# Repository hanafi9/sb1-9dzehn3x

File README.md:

# sb1-9dzehn3x

[Edit in StackBlitz next generation editor ⚡️](https://stackblitz.com/~/github.com/hanafi9/sb1-9dzehn3x)

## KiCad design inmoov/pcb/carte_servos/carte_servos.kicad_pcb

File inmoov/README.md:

# InMoov : Raspberry Pi 5 + Coral USB

Deux programmes qui tournent **à côté de MyRobotLab (Nixie)** sur le Raspberry Pi 5
et lui parlent par son API REST (`http://127.0.0.1:8888/api/service/...`) :

| Programme | Rôle | Python |
|---|---|---|
| `vision/face_tracker.py` | Caméra USB → Coral USB → tourne `rothead` / `neck` vers le visage le plus proche | **3.12** (PyCoral n'existe pas pour 3.13 ; installé par `vision/install_coral.sh`) |
| `voice/speech_listener.py` | Micro → détection de voix → Whisper → commandes locales, **IA Claude** ou chatbot `i01.chatBot` | 3.11 (celui du système) |
| `voice/llm_brain.py` | IA conversationnelle (Claude) qui remplace le chatbot AIML et peut bouger la tête et les mains | 3.11 |
| `legs/` | Jambes motorisées : firmware Arduino Mega, pilotage depuis le Pi, calcul des moteurs | Arduino + 3.11 |
| `app/` | **Atelier InMoov** : application web pour tout monter, programmer et régler (voir section 0) | 3.11 |

```
 Caméra USB ─► face_tracker.py (Coral) ──┐  POST /api/service/i01.head.rothead/moveTo [95.0]
                                         ├─► MyRobotLab Nixie (InMoov2) ─► Arduino Mega ─► servos
 Micro USB ──► speech_listener.py ───────┘  POST /api/service/i01.chatBot/getResponse ["bonjour"]
                                                         └─► htmlFilter ─► i01.mouth (synthèse vocale)
```

## 0. Atelier InMoov : l'application qui regroupe tout

Une application web qui tourne sur le Raspberry Pi et s'ouvre depuis un téléphone, une
tablette ou un PC du même réseau : `http://<adresse-du-pi>:8090`.

| Onglet | Ce qu'il fait |
|---|---|
| **Tableau de bord** | État de MyRobotLab, du Coral, des ports série, des services, avancement du montage |
| **Banc d'essai** | Tout tester sur une page : **silhouette du robot cliquable** (tête, torse, bras, mains) avec curseurs et balayage de chaque servo, bilan ✓/✗ qui colore la silhouette, **les 2 caméras en direct** avec les cadres des visages et objets vus par le Coral, haut-parleurs gauche/droite, **faire parler** le robot (Piper), niveau du **micro**, « tout au repos » et **arrêt** (servos coupés). 2e caméra : `vision.second_camera_index` |
| **Documentation** | **Le manuel complet** : un chapitre par partie du corps (tête et cou, torse et électronique, bras, mains, bassin, jambes, capteurs) avec rôle, servos, schéma de câblage, pièces, montage pas à pas, réglages, test final, problèmes fréquents et liens officiels ; plus logiciel, IA, dépannage général et tous les liens. Recherche intégrée et bouton « Tout imprimer / PDF ». Version PDF prête : [docs/manuel-inmoov.pdf](docs/manuel-inmoov.pdf) |
| **Guide de montage** | 43 étapes en 10 phases (Pi, MyRobotLab, électronique, tête et cou, bras/mains/torse, vision, voix et IA, jambes, mise en service, nouveautés IA et capteurs), à cocher, avec les commandes à copier |
| **Schémas** | Un schéma de câblage par partie (tête, torse, bras, mains, bassin, jambes) généré automatiquement, la liste des servos (modèle, carte, canal), les **pièces imprimées à cocher**, le matériel, et l'**électronique simplifiée** : une seule Arduino Mega + 3 cartes PCA9685, avec le script MyRobotLab qui rattache chaque servo à sa carte |
| **Schémas électriques** (dans l'onglet Schémas) | **8 schémas détaillés** : alimentation générale, tête, cou, torse, bras, mains, bassin, jambes. Chaque fil, chaque broche, chaque fusible, avec la **liste de câblage** (de → à, type, couleur, section) et les points de vigilance. PDF prêt : [docs/schemas-electriques.pdf](docs/schemas-electriques.pdf). **Projet KiCad** : dossier [kicad/](kicad/LISEZMOI.md) ou bouton « Projet KiCad (.zip) » |
| **Circuits imprimés « DOMOKAMI CONNECT »** | Prêts à commander, avec Gerber, liste des composants, contrôle KiCad (0 erreur) et mode d'emploi : [shield jambes](pcb/shield_jambes/LISEZMOI.md) pour l'Arduino Mega n°2 ; [carte servos 16 voies](pcb/carte_servos/LISEZMOI.md) × 3 (PCA9685 + fusible + mesure de courant, puces posées par JLCPCB) ; [HAT capteurs](pcb/hat_capteurs/LISEZMOI.md) pour le Raspberry Pi 5 (3 ADS1115 + 10 entrées FSR + 3 sorties I2C) |
| **Capteurs** | Courant et tension de chaque carte (coupure automatique si un servo force), batterie, toucher au bout des doigts, présence, bouton « prise douce » |
| **IA** | État de l'IA (Claude, vision, IA locale, voix Piper, LED), **souvenirs** du robot (à consulter ou effacer), **gestes appris** à rejouer |
| **Servos** | Les 31 servos d'InMoov2 (tête et cou, torse, bras, mains) : curseur pour bouger, repos, activer/désactiver, lire la position, **calibration** (min, max, repos, vitesse, sens), envoi à MyRobotLab et enregistrement de sa configuration |
| **Arduino** | Voir le code, **compiler et téléverser** MrlComm (les deux Mega du haut du corps) et le firmware des jambes, installer le cœur AVR et les bibliothèques, détecter les cartes branchées |
| **Jambes** | Connexion à l'Arduino des jambes, état de chaque servo (position, charge, température, tension), RESET, FIGER, couple, poses et séquences (mouvement seulement si « robot sur portique » est coché), **pieds et équilibre** : poids et centre de pression de chaque pied, tare, équilibre surveillé ou actif |
| **Services** | Démarrer, arrêter et voir le journal du suivi de visage et de la voix |
| **Réglages** | Adresse et dossier de MyRobotLab, arduino-cli, édition **vérifiée** de `config.json` et de la config des jambes (copie `.bak` à chaque enregistrement) |

### Électronique simplifiée (onglet Schémas)

Au lieu de brancher chaque servo sur deux Arduino Mega, on utilise **une seule Mega** (i01.left,
programme MrlComm) et **3 cartes PCA9685** de 16 voies reliées par un bus I2C à 4 fils
(service MyRobotLab `Adafruit16CServoDriver`) :

| Carte | Adresse | Pont à souder | Servos |
|---|---|---|---|
| A | 0x40 | aucun | tête (8) + ventre (3) |
| B | 0x41 | A0 | bras gauche (4) + main gauche (6) |
| C | 0x42 | A1 | bras droit (4) + main droite (6) |

Le bouton **« Appliquer à MyRobotLab »** (ou le script à coller dans l'onglet Python de MyRobotLab)
crée les 3 cartes, les attache à `i01.left` en I2C (`attach("i01.left", "0", "0x40")`, comme dans
l'exemple officiel de MyRobotLab) puis fait pour chaque servo `detach()`, `setPin(canal)`, `attach(carte)`.
Enregistrez ensuite la config MyRobotLab (onglet Servos).

Pourquoi passer par l'Arduino et pas directement par le Raspberry Pi 5 ? Le service RasPi de
MyRobotLab repose sur Pi4J 1.x / wiringPi, qui ne gère pas le Pi 5.

Alimentation : 6 V forte puissance → bornier avec un fusible par carte ; pour les gros servos,
+ et − pris directement sur le bornier et seulement le signal sur la carte ; masses toutes reliées.

### Installation

```bash
cd ~/domokami/inmoov
python3 -m venv .venv-app
.venv-app/bin/pip install -r app/requirements.txt
sudo usermod -aG dialout $USER         # accès aux ports série (Arduino), puis redémarrer

# arduino-cli (compilation et téléversement depuis l'appli)
curl -fsSL https://raw.githubusercontent.com/arduino/arduino-cli/master/install.sh | BINDIR=$HOME/.local/bin sh

# mot de passe de l'appli (conseillé : elle peut bouger le robot et reprogrammer les cartes)
echo 'INMOOV_APP_PASSWORD=choisissez-un-mot-de-passe' > app.env && chmod 600 app.env

cd app && set -a && . ../app.env && set +a && ../.venv-app/bin/python app.py
```

Pour que les boutons Démarrer / Arrêter de l'onglet Services fonctionnent, autorisez **uniquement**
ces commandes sans mot de passe (`sudo visudo -f /etc/sudoers.d/inmoov`), en remplaçant
`VOTRE_UTILISATEUR` par votre nom d'utilisateur (la commande `whoami` l'affiche) :

```
VOTRE_UTILISATEUR ALL=(root) NOPASSWD: /usr/bin/systemctl start inmoov-vision, /usr/bin/systemctl stop inmoov-vision, /usr/bin/systemctl restart inmoov-vision, /usr/bin/systemctl start inmoov-voice, /usr/bin/systemctl stop inmoov-voice, /usr/bin/systemctl restart inmoov-voice, /usr/bin/systemctl start inmoov-sensors, /usr/bin/systemctl stop inmoov-sensors, /usr/bin/systemctl restart inmoov-sensors
```

Démarrage automatique : service `systemd/inmoov-app.service` (voir section 5).

**Sans ligne de commande** : onglet Services → « Programmes du robot ». L'Atelier lance lui-même
MyRobotLab, les caméras (Coral), la voix et les capteurs, avec leurs journaux en direct
(`app/data/logs/`). Cochez « au démarrage de l'Atelier » pour qu'ils se lancent tout seuls ; il suffit
alors d'installer le seul service de l'Atelier : `bash systemd/install.sh` puis
`sudo systemctl enable --now inmoov-app`.

### Bon à savoir

- Le curseur d'un servo envoie une valeur **de 0 à 180** que MyRobotLab convertit entre **min** et
  **max** (c'est le fonctionnement d'InMoov2). Les valeurs par défaut affichées viennent du code
  de MyRobotLab (InMoov2HeadConfig, InMoov2ArmConfig, InMoov2HandConfig, InMoov2TorsoConfig).
- « Enregistrer + appliquer » envoie `setMinMaxOutput`, `setInverted`, `setRest` et `setSpeed` au servo ;
  « Enregistrer la config MyRobotLab » appelle `runtime.saveConfig` pour que ce soit conservé au redémarrage.
- MrlComm est pris dans le dossier de MyRobotLab (`<mrl_dir>/resource/Arduino/MrlComm`) pour être
  toujours de la même version que MyRobotLab. **Arrêtez MyRobotLab** (ou déconnectez la carte) avant
  de téléverser : le port série ne peut pas servir à deux programmes.
- Testée avec un faux MyRobotLab et un faux Arduino des jambes : le firmware des jambes a été
  **réellement compilé depuis l'appli**. Elle n'a pas encore été essayée avec le vrai robot.

## 1. Préparer le Raspberry Pi 5

- Raspberry Pi OS **64 bits** (Bookworm ou Trixie), alimentation officielle **5 V / 5 A**
  (sinon les ports USB sont limités à 600 mA, insuffisant pour Coral + caméra + micro).
- Brancher le **Coral USB sur un port USB 3 (bleu)**.
- MyRobotLab Nixie installé et InMoov2 démarré (WebGui sur le port 8888).
- **Désactiver le suivi de visage intégré d'InMoov2** pour ne pas avoir deux programmes qui
  bougent la tête en même temps.

Télécharger le projet sur le Pi (il arrive dans `~/domokami/inmoov`, quel que soit votre nom
d'utilisateur), puis :

```bash
sudo apt install -y git python3-venv
git clone --branch claude/inspiring-fermi-0kap3c https://github.com/hanafi9/sb1-9dzehn3x.git ~/domokami
cd ~/domokami/inmoov
cp config.example.json config.json   # puis l'adapter à votre robot
```

Mettre à jour plus tard : `cd ~/domokami && git pull` (config.json et les fichiers .env sont conservés).

## 2. Vision : Coral USB + suivi de visage

### Installation (pilote + Python + modèle) : un seul script

```bash
cd ~/domokami/inmoov
bash vision/install_coral.sh        # sans sudo ; redémarrer le Pi s'il le demande
```

Le script installe :
1. le pilote **libedgetpu** ;
2. **Python 3.12** (avec [uv](https://docs.astral.sh/uv/), à côté du Python du système) ;
3. **pycoral**, **tflite-runtime** et OpenCV dans `.venv-vision` ;
4. le modèle de détection de visage.

Il vérifie l'empreinte SHA-256 de chaque fichier téléchargé et finit par afficher le Coral vu
par PyCoral.

> Pourquoi pas les paquets de Google ? Le dépôt apt Coral de Google répond « 403 Forbidden »
> depuis fin septembre 2026, et le PyCoral officiel s'arrête à Python 3.9. Le script prend les
> versions recompilées par la communauté : [feranick/libedgetpu](https://github.com/feranick/libedgetpu/releases)
> (paquet Debian 13 « trixie »), [feranick/pycoral](https://github.com/feranick/pycoral/releases) et
> [feranick/TFlite-builds](https://github.com/feranick/TFlite-builds/releases).

`lsusb` affiche `1a6e:089a Global Unichip` tant que le Coral n'a pas servi, puis
`18d1:9302 Google` une fois initialisé par le suivi de visage (il passe alors en USB 3).
⚠️ Le Coral peut consommer jusqu'à 900 mA : alimentation officielle 27 W (5 A) ou hub USB alimenté.

### Modèle de détection de visage

Déjà téléchargé par `install_coral.sh` dans `models/`. À la main :

```bash
mkdir -p models
wget -P models https://raw.githubusercontent.com/google-coral/test_data/master/ssd_mobilenet_v2_face_quant_postprocess_edgetpu.tflite
```

### Lancer

```bash
cd vision
../.venv-vision/bin/python face_tracker.py --config ../config.json --dry-run -v   # test sans bouger la tête
../.venv-vision/bin/python face_tracker.py --config ../config.json
```

### Réglages (`config.json` → `vision`)

| Clé | Effet |
|---|---|
| `pan.invert` / `tilt.invert` | La tête part dans le mauvais sens ? Passez à `true` / `false`. |
| `gain` | Vitesse de réaction. Trop grand = la tête oscille ; trop petit = elle traîne. |
| `deadband` | Zone morte au centre de l'image (0.08 = 8 %), pour éviter les tremblements. |
| `max_step` | Nombre maximum de degrés par commande (protège les servos). |
| `min` / `max` | **Mettez les mêmes limites que dans MyRobotLab** pour ne jamais forcer la mécanique. |
| `show_window` | `true` pour voir l'image et les visages détectés (écran nécessaire). |

## 3. Reconnaissance vocale améliorée

Améliorations par rapport à la reconnaissance d'origine :

1. **Whisper (faster-whisper) hors ligne** : bien meilleur en français, pas besoin d'Internet.
2. **Détection de voix (WebRTC VAD)** : Whisper n'est appelé que quand quelqu'un parle,
   ce qui économise le processeur et évite les phrases inventées sur le bruit des servos.
3. **Filtres anti-erreurs** : on ignore les segments à faible confiance et les « hallucinations »
   connues de Whisper en français (« Sous-titres réalisés par la communauté d'Amara.org »...).
4. **Mot de réveil tolérant** : « InMoov », « In Moov », « Inmove » sont tous acceptés.
   Dire juste « InMoov » → le robot répond « oui ? » et écoute la phrase suivante.
5. **Vocabulaire** (`vocabulary`) : les mots donnés aident Whisper à bien écrire les noms propres.
6. **Commandes locales** instantanées (`commands`), avec tolérance aux petites erreurs ;
   tout le reste part au chatbot d'InMoov2.
7. **Le micro est ignoré pendant que le robot parle** (durée estimée d'après la longueur de la réponse).

### Installation

```bash
sudo apt install -y libportaudio2
python3 -m venv .venv-voice
.venv-voice/bin/pip install -r voice/requirements.txt
cd voice
../.venv-voice/bin/python speech_listener.py --list-devices      # trouver le numéro du micro
../.venv-voice/bin/python speech_listener.py --config ../config.json --dry-run
```

Au premier lancement, le modèle Whisper est téléchargé (environ 150 Mo pour `base`).

### Choix du modèle Whisper (`whisper_model`)

| Modèle | Français | Vitesse sur Pi 5 |
|---|---|---|
| `tiny` | moyen | le plus rapide (≈ 2-3 s pour 10 s d'audio) |
| `base` | **bon compromis (par défaut)** | rapide |
| `small` | très bon | plus lent, à tester selon votre patience |

Les phrases adressées au robot sont courtes (2 à 4 s), donc le temps de réponse
est bien plus court que pour 10 s d'audio.

### Le matériel compte autant que le logiciel

- Un **micro USB de conférence** ou un **ReSpeaker USB Mic Array** (avec réduction de bruit)
  donne de bien meilleurs résultats qu'une webcam ou un micro jack.
- Placez le micro **loin des servos et du ventilateur** du Pi, idéalement dans la tête, orienté vers l'avant.
- Trop de fausses détections ? Montez `vad_aggressiveness` à 3.
  Le robot ne vous entend pas ? Descendez-le à 1.

## 4. IA conversationnelle (Claude) à la place du chatbot d'InMoov2

Quand `brain.enabled` vaut `true` dans `config.json`, les phrases qui ne sont pas des
commandes locales partent vers **Claude** (API Anthropic) au lieu du chatbot AIML :

- réponses naturelles en français, courtes et adaptées à la synthèse vocale ;
- **mémoire de la conversation** (remise à zéro après 10 min de silence, `reset_after_idle_s`) ;
- Claude peut **tourner la tête, ouvrir/fermer les mains, revenir au repos** (outils `move_head`,
  `hand`, `rest_position`), toujours dans les limites de `config.json` ;
- **les jambes ne sont pas accessibles à l'IA**, volontairement ;
- si Internet ou l'API ne répond pas, le robot **repasse automatiquement sur le chatbot d'InMoov2** ;
- si Claude refuse une demande, l'API la relance sur le modèle de secours recommandé
  (option `fallbacks: "default"`), sinon le robot dit poliment qu'il ne répond pas.

### Mise en route

1. Créer une clé API sur <https://platform.claude.com> (l'usage est payant, au nombre de mots traités).
2. Sur le Pi :
   ```bash
   echo 'ANTHROPIC_API_KEY=sk-ant-...' > ~/domokami/inmoov/anthropic.env
   chmod 600 ~/domokami/inmoov/anthropic.env      # ce fichier ne doit jamais aller sur GitHub
   ```
3. Dans `config.json` → `brain` : mettre votre prénom dans `owner_name`, le nom du robot dans
   `robot_name`, et éventuellement des consignes dans `extra_instructions`
   (« Tu tutoies tout le monde », « Tu adores l'astronomie »...).
4. Test sans bouger le robot : `../.venv-voice/bin/python speech_listener.py --config ../config.json --dry-run`
   (avec la clé chargée : `set -a; . ../anthropic.env; set +a`).

| Clé `brain` | Effet |
|---|---|
| `model` | `claude-opus-5-5` par défaut |
| `effort` | `low` = réponses plus rapides et moins chères (bien pour la conversation) ; `medium`/`high` = plus réfléchi mais plus lent |
| `max_tool_rounds` | nombre maximum de gestes enchaînés pour une même phrase |
| `*_service`, `*_min`, `*_max` | noms des services MyRobotLab et limites des mouvements autorisés à l'IA |

## 5. Démarrage automatique

```bash
cd ~/domokami/inmoov
bash systemd/install.sh            # adapte l'utilisateur et les chemins, puis copie les services
sudo systemctl enable --now inmoov-app inmoov-vision inmoov-voice inmoov-sensors
journalctl -u inmoov-voice -f      # voir ce que le robot entend
```

## 6. Tests (sans matériel)

```bash
python3 -m unittest discover -s tests -v
```

Ces tests vérifient l'Atelier (avec un faux MyRobotLab, si Flask est installé), la logique de suivi, le découpage audio, le mot de réveil, les commandes,
le format des appels à MyRobotLab (avec un faux serveur), le cerveau Claude (avec un faux client,
si le paquet `anthropic` est installé), les poses des jambes, la cohérence des limites
entre le Pi et le firmware Arduino, et le calcul de couple.
Ils **ne remplacent pas** un essai réel avec le Coral, la caméra et le micro.

## 7. Jambes motorisées

> ⚠️ **Sécurité d'abord.** Un robot de cette taille qui tombe se casse et peut blesser.
> Tous les essais se font **robot accroché à un portique** (sangle au niveau du bassin),
> avec un **arrêt d'urgence matériel qui coupe l'alimentation des servos**.
> Le firmware ajoute des protections, il ne remplace pas ces deux-là.

Les jambes publiées par Gaël Langevin sont prévues pour tenir debout ; il n'existe pas de
version motorisée officielle. Ce dossier fournit une base pour **12 articulations**
(6 par jambe : hanche lacet / roulis / tangage, genou, cheville tangage / roulis).

### 7.1 Choisir les moteurs : d'abord peser le robot

```bash
cd legs
python3 torque_calc.py --masse 18                 # remplacez 18 par la masse réelle portée par les jambes
python3 torque_calc.py --masse 18 --reduction 4   # avec une réduction 4:1 (poulies/engrenages)
```

Exemple **pour 18 kg** (valeur d'exemple, pas la masse de votre robot), coefficient de sécurité 1,5 :

| Articulation | Couple sans réduction | Avec réduction 4:1 |
|---|---|---|
| Genou (accroupi 40°, 2 pieds) | 176 kg·cm | 44 kg·cm |
| Hanche roulis / cheville roulis (sur 1 pied) | 243 kg·cm | 61 kg·cm |
| Cheville tangage (sur 1 pied) | 135 kg·cm | 34 kg·cm |
| Hanche tangage | 68 kg·cm | 17 kg·cm |
| Hanche lacet | 24 kg·cm | 6 kg·cm |

Actionneurs comparés (couple continu retenu ≈ 1/3 du couple de blocage quand le fabricant
ne donne pas de couple nominal) :

| Actionneur | Couple | Bus | Compatible avec le firmware fourni |
|---|---|---|---|
| Feetech STS3215 12 V | 30 kg·cm blocage | TTL 1 Mbit/s | oui |
| Feetech STS3250 12 V | 50 kg·cm blocage, 16 nominal | TTL 1 Mbit/s | oui |
| RSBL85-12 (Waveshare/Feetech) | 85 kg·cm | à vérifier avant achat | à vérifier |
| Feetech SM-1500 12 V | 180 kg·cm blocage | RS485, 115200 bauds | même protocole, mais adaptateur RS485 et `BUS_BAUD` à changer |
| MyActuator RMD-X8 Pro | 8 N·m nominal (≈ 82 kg·cm), 48 V | CAN | non (firmware à adapter) |

**Conclusion honnête :** sans réduction, **aucun servo « bus » de cette liste ne tient le robot
sur une jambe** dès qu'il pèse une quinzaine de kilos. Pistes réalistes :

1. **Commencer par les mouvements à deux pieds** (flexions, balancement léger), où les couples sont
   bien plus faibles ;
2. ajouter une **réduction 3:1 à 5:1** (poulies crantées GT2/HTD) sur genoux, hanches et chevilles ;
3. utiliser des **SM-1500** (ou plus gros) pour genoux, chevilles et roulis de hanche, et des
   **STS3250** pour les lacets de hanche ;
4. **alléger le haut du corps** (remplissage d'impression réduit, batteries dans le bassin) ;
5. la **marche** ne viendra qu'ensuite, avec le portique, très lentement.

### 7.2 Câblage

```
Raspberry Pi 5 ──USB──► Arduino Mega 2560
                         ├─ Serial1 (TX1 18 / RX1 19) ─► adaptateur bus Feetech (half-duplex) ─► servos 1-6, 11-16
                         ├─ I2C (SDA 20 / SCL 21) ──────► BNO085 (centrale inertielle) dans le bassin
                         └─ broche 2 ◄── bouton d'arrêt d'urgence (contact NF vers GND)
Alimentation servos 12 V forte puissance ─► via le contact de l'arrêt d'urgence ─► servos
Masse commune Arduino / adaptateur / alimentation servos
```

Numérotation : jambe gauche ID 1 à 6, jambe droite ID 11 à 16, dans l'ordre
hanche lacet, hanche roulis, hanche tangage, genou, cheville tangage, cheville roulis.
Programmez l'ID de chaque servo **un par un** (logiciel FD de Feetech) avant de les chaîner.

### 7.3 Firmware Arduino (`legs/firmware/inmoov_legs/`)

Bibliothèques à installer : **SCServo** et **Adafruit BNO08x**. Carte : *Arduino Mega 2560*.
Le firmware a été compilé pour la Mega (37 Ko de flash, 4,3 Ko de RAM) ; il n'a pas encore tourné
sur de vrais servos.

Protections intégrées : limites de position par articulation, arrêt si un servo ne répond plus,
dépasse **65 °C** ou reste en **surcharge** ; arrêt si le bassin penche de plus de **20°** ;
arrêt si le Pi n'envoie plus de battement de cœur pendant 1 s ; bouton d'arrêt d'urgence.
En défaut, les articulations sont **figées** (pas de coupure du couple, sinon le robot s'effondre)
et tout mouvement est refusé jusqu'à la commande `RESET`. **Au démarrage, le firmware est en défaut.**

### 7.4 Calibration puis premiers mouvements

1. Jambes tendues, robot sur le portique : calibrer le milieu de chaque servo (position 2048)
   avec le logiciel FD de Feetech.
2. Resserrer `POS_MIN` / `POS_MAX` dans le firmware selon votre mécanique.
3. Côté Pi :
   ```bash
   python3 -m venv .venv-legs && .venv-legs/bin/pip install -r legs/requirements.txt
   cd legs
   cp legs_config.example.json legs_config.json
   ../.venv-legs/bin/python legs_controller.py --config legs_config.json check     # vérifie les poses
   ../.venv-legs/bin/python legs_controller.py --config legs_config.json status
   ../.venv-legs/bin/python legs_controller.py --config legs_config.json reset
   ../.venv-legs/bin/python legs_controller.py --config legs_config.json pose test_genoux_5deg
   ```
4. **Vérifier le sens de chaque articulation** avec de petits angles. Si une articulation part à
   l'envers, mettre sa `direction` à `-1` dans `legs_config.json`.
5. Seulement ensuite : `pose flexion_legere`, puis `sequence flexions` et `sequence balancement`.

Les poses sont en degrés (0 = debout). Une pose hors limites est **refusée**, pas rabotée.

### 7.5 Capteurs d'équilibre pour la marche

Deux capteurs, comme sur les robots humanoïdes de la RoboCup :

- la **centrale BNO085** au centre du bassin (inclinaison + gyroscope) ;
- **4 cellules de charge par pied** (une à chaque coin, entre la plaque fixée à la cheville et la
  semelle ; cellule 4 fils, ou 3 fils complétée par 2 résistances de 1 kΩ), chacune avec un
  **HX711** (couper la piste RATE-GND et relier RATE au VCC = 80 mesures/s) sur l'Arduino Mega n°2 :
  cellule n → DOUT = broche 22 + 2n, SCK = 23 + 2n (ordre : pied gauche avant-ext, avant-int,
  arrière-ext, arrière-int, puis pied droit). Elles donnent le **poids sur chaque pied** et le
  **centre de pression**. Les capteurs FSR ne conviennent pas : ils saturent vers 10 N.

Le firmware corrige les chevilles **50 fois par seconde** (« stratégie de cheville ») : correction
bornée (`max_deg`, 10° au plus), progressive, remise à zéro si les pieds quittent le sol, en cas de
défaut ou sur FIGER. Commandes série ajoutées : `FEET`, `TARE`, `CAL`, `BALCFG`, `BAL 0|1|2`.

```bash
cd legs
python3 legs_controller.py --config legs_config.json feet tare          # pieds EN L'AIR
python3 legs_controller.py --config legs_config.json feet cal 0 2000    # 2 kg posés sur la cellule 0
python3 legs_controller.py --config legs_config.json balance monitor    # calcule sans bouger
python3 legs_controller.py --config legs_config.json balance on
python3 legs_controller.py --config legs_config.json sequence pas_sur_place
```

En mode `monitor`, penchez le robot à la main vers l'avant : `corr_tangage` doit devenir **négatif**
(pointes vers le bas), sinon mettez `balance.imu_pitch_sign` à `-1` ; idem à droite pour le roulis.
Une étape de séquence peut exiger un appui : `["transfert_gauche", 3000, {"appui": "gauche", "min": 0.85}]`.
Si le pied ne porte pas 85 % du poids, les jambes se **figent** au lieu de lever l'autre pied.
C'est une marche lente « quasi statique » ; tout se règle aussi dans l'onglet **Jambes** de l'Atelier.

## 8. Nouveautés : IA et capteurs, inspirés de l'état de l'art

Le comparatif complet avec ce qui se fait ailleurs (LeRobot, modèles vision-langage-action,
Unitree G1, Raspberry Pi AI HAT+ 2…) est dans [docs/veille-robotique.md](docs/veille-robotique.md).

### 8.1 Une IA qui voit, fait des gestes et se souvient

Dans `config.json` → `brain` :

| Clé | Effet |
|---|---|
| `camera_frame_path` | image partagée par le suivi de visage (`vision.share_frame_path`, par défaut `/dev/shm/inmoov_frame.jpg`) : l'IA peut **regarder** (« qu'est-ce que je tiens ? ») |
| `gestures` | gestes d'InMoov2 que l'IA a le droit de lancer (`i01.execGesture`) |
| `recorded_gestures_dir` | gestes **appris par imitation**, aussi jouables par l'IA |
| `memory_path` | **souvenirs** : l'IA retient prénoms et informations (outil `remember`), visibles et effaçables dans l'onglet IA |

### 8.1 bis « Raisonnement humain » : perception, réflexion, humeur et souvenirs

Section `brain` (+ `brain.mind`), programmes `voice/mind.py`, `perception.py`, `mood.py`,
`episodes.py`, `reasoning.py` et `vision/scene.py` :

| Capacité | Comment | Réglage |
|---|---|---|
| **Étudier l'environnement avec le Coral** | `face_tracker.py` détecte aussi les **objets de la pièce** (SSDLite MobileDet, 80 catégories COCO, noms en français) sur le même Coral USB, toutes les 2 s, et écrit ce qu'il voit dans `/dev/shm/inmoov_vision.json`. La voix retient ce qui apparaît, disparaît, et ce qui est « habituel » dans la pièce. **Aucune image n'est envoyée sur Internet pour cela.** | `vision.objects`, `brain.mind` |
| **Réagir de lui-même à ce qu'il voit** | `voice/reactions.py` surveille les caméras et fait parler le robot **sans qu'on lui parle** : il **salue** quelqu'un qui arrive (par son prénom s'il le reconnaît), réagit à un **visage tout près**, engage la conversation avec quelqu'un qui **reste sans rien dire**, remarque un **objet inhabituel**, dit **au revoir** à la personne qui part. Délais minimum, limite par heure et silence la nuit. On peut répondre sans redire le mot de réveil. | `brain.reactions` |
| **Reconnaître votre voix** | Empreinte vocale calculée sur le Pi (sherpa-onnx, modèle WeSpeaker ~27 Mo) : `voice/enroll_voice.py <prénom>` enregistre 6 phrases, puis Claude sait qui parle (« [Voix de …] ») et peut réserver les mouvements à une seule voix. Pas un verrou de sécurité. | `voice.speaker_id` |
| **Reconnaissance vocale en ligne** | `voice/cloud_stt.py` : la phrase est transcrite par Groq (`whisper-large-v3-turbo`) ou OpenAI (`gpt-4o-mini-transcribe`), bien plus juste et rapide que Whisper sur le Pi ; Whisper local en secours sans Internet. Clé dans `anthropic.env`. | `voice.cloud_stt` |
| **Agir sur la maison (Home Assistant)** | Outil `home_assistant` : Kamil envoie des phrases simples à l'assistant **Assist** de Home Assistant (`POST /api/conversation/process`), ex. « allume la lumière du salon », « quelle est la température de la chambre ? ». Seuls les appareils **exposés à Assist** sont accessibles ; jeton dans `anthropic.env` (`HOME_ASSISTANT_TOKEN`) ; réservable à votre voix. | `brain.home_assistant` |
| **Surveiller ce qui se passe autour** | `voice/watch.py` tient un journal (arrivées et départs de personnes, mouvements sans personne, objets apparus ou disparus) sur les 2 caméras, avec photos. « Qu'est-ce qui s'est passé pendant mon absence ? », « montre-moi qui est passé ». **Mode garde** : Kamil interpelle la personne et Home Assistant prévient le téléphone. | `brain.watch` |
| **Voix jeune et claire** | `voice/tts_cloud.py` : voix en ligne OpenAI `gpt-4o-mini-tts` (voix `ash`, jeune homme de 28 ans, légèrement aiguë) ; Piper en secours sans Internet, sans alterner les deux voix. Écouter : `voices_test.py --cloud`. | `voice.cloud_tts` |
| **Kamil en mode kiosque** | `http://<pi>:8090/kiosk` : l'onglet Kamil seul, en plein écran, pour l'écran du robot ou une tablette (pas de mot de passe depuis le Pi lui-même). Ouverture automatique sur l'écran du Pi : `bash tools/install_kiosk.sh`. | — |
| **Onglet « Kamil » de l'Atelier** | Visage animé (veille, écoute, réflexion, parole), conversation en direct en bulles, écrire à Kamil ou lui faire dire une phrase, humeur, voix reconnue, caméra, mode garde. `voice/kamil_bridge.py` relie la voix à l'Atelier par `/dev/shm`. | `voice.app_bridge` |
| **Kamil dans Home Assistant** | `voice/ha_mqtt.py` : appareil « Kamil » créé tout seul par MQTT (état, phrase entendue, réponse, voix, personnes, mouvement, journal, mode garde, 2 caméras ; « Dire » et « Question » pour les automatisations). Voir `docs/home_assistant_mqtt.md`. | `mqtt` |
| **Ignore la télé et la radio** | Sans « Kamil » : longues phrases (> 8 s) et voix inconnues ignorées ; Claude répond `[silence]` si ce n'était pas pour lui. | `voice.follow_up_max_audio_s`, `voice.speaker_id.follow_up_known_voices_only` |
| **Regarder autour de lui** | outil `look_around` : la tête va à gauche, au centre, à droite (suivi de visage suspendu), 3 photos envoyées à Claude | `brain.tracking_pause_path` |
| **Réfléchir selon la question** | bavardage = effort `low` ; « pourquoi », « comment », conseil, calcul, histoire… = effort `high`, et le robot dit « laisse-moi réfléchir ». Le changement passe par un « effort par message » (le cache de la conversation reste valable). Il admet quand il ne sait pas. | `adaptive_effort`, `effort`, `effort_think`, `say_thinking` |
| **Conscience de la situation** | à chaque phrase, Claude reçoit l'heure, ce que voit le Coral, la batterie, la distance, le toucher, les défauts de servos et son humeur (message système valable un seul tour) | `brain.mind` |
| **Humeur et personnalité** | énergie, joie et curiosité évoluent (nuit, batterie, solitude, échanges) ; l'IA peut exprimer une émotion avec l'outil `feel`. Modèle simple et assumé : le robot ne prétend pas ressentir comme un humain. | `brain.mind.mood_path` |
| **Mémoire des conversations** | à la fin d'une conversation (10 min de silence), Claude en écrit un résumé ; les 8 derniers sont donnés au début des suivantes | `brain.mind.episodes_path`, `episodes_in_prompt` |

Fichiers créés dans `data/` : `environment.json`, `mood.json`, `episodes.json` (effaçables à tout moment).
Coût : un petit appel à l'API de plus par conversation (le résumé) ; les questions « à réfléchir »
coûtent plus que le bavardage. Installation du modèle d'objets : relancer `bash vision/install_coral.sh`.

Section `local_llm` : **IA de secours sans Internet** (Ollama sur le Pi, ou hailo-ollama avec le
Raspberry Pi AI HAT+ 2). Ordre utilisé : Claude → IA locale → chatbot d'InMoov2.

Section `leds` : **LED d'état** NeoPixel (bleu = écoute, violet = réfléchit, vert = parle, rouge = défaut).

### 8.2 Voix française hors ligne (Piper)

```bash
.venv-voice/bin/pip install piper-tts
mkdir -p models && .venv-voice/bin/python -m piper.download_voices --download-dir models fr_FR-tom-medium
```
Puis `"tts": "piper"` dans la section `voice`. Voix françaises : `fr_FR-tom-medium` (homme),
`fr_FR-siwis-medium` (femme), `fr_FR-upmc-medium`, `fr_FR-gilles-low`. Avec Piper, le micro est
coupé exactement pendant que le robot parle.

### 8.3 Mode imitation et gestes appris (`vision/mirror.py`)

Le robot **copie vos bras et vos doigts** devant la caméra (MediaPipe Pose + Hands), en miroir,
et peut **enregistrer** le mouvement pour le rejouer (onglet IA, ou « InMoov, fais le geste salut »).

```bash
python3 -m venv .venv-mirror && .venv-mirror/bin/pip install -r vision/requirements-mirror.txt
sudo systemctl stop inmoov-vision             # la caméra ne sert qu'à un programme
cd vision
../.venv-mirror/bin/python mirror.py --config ../config.json --dry-run -v   # sans bouger le robot
../.venv-mirror/bin/python mirror.py --config ../config.json --record salut
```
Section `mirror` : articulations activées (l'omoplate est désactivée par défaut), vitesse maximale,
lissage. Vérifié sur des photos de test MediaPipe : poing fermé, index levé, pouce levé et main
ouverte sont bien reconnus ; bras tendus sur les côtés → omoplate au maximum, épaule ≈ 0.
**Pas encore essayé sur le vrai robot** : commencez en `--dry-run`, vitesse basse, personne à
portée des bras.

### 8.4 Capteurs (`sensors/sensor_hub.py`)

Sur le bus I2C du Raspberry Pi 5 (le Pi gère très bien l'I2C en Python ; seul MyRobotLab ne le peut pas) :

| Capteur | Rôle |
|---|---|
| INA226 × 4 | courant et tension de chaque carte PCA9685 + batterie ; **coupure automatique** des servos d'une carte qui force trop longtemps |
| ADS1115 × 3 + FSR × 10 | force au bout de chaque doigt ; bouton **« prise douce »** |
| VL53L1X | distance de la personne la plus proche ; salut automatique facultatif (`greet_text`) |

```bash
sudo raspi-config nonint do_i2c 0 && sudo apt install -y i2c-tools && i2cdetect -y 1
python3 -m venv .venv-sensors && .venv-sensors/bin/pip install -r sensors/requirements.txt
cd sensors && ../.venv-sensors/bin/python sensor_hub.py --config ../config.json --simulate   # essai sans capteurs
```
**Important :** le module INA226 courant a un shunt de 0,1 Ω (0,8 A maximum). Pour des servos,
remplacez-le par un shunt de 1 à 2 mΩ et indiquez sa valeur (`shunt_ohm`). Les limites de
courant (`max_current_a`) sont des valeurs de départ : ajustez-les après avoir mesuré votre robot.
Câblage et adresses : onglet **Schémas → Capteurs**.

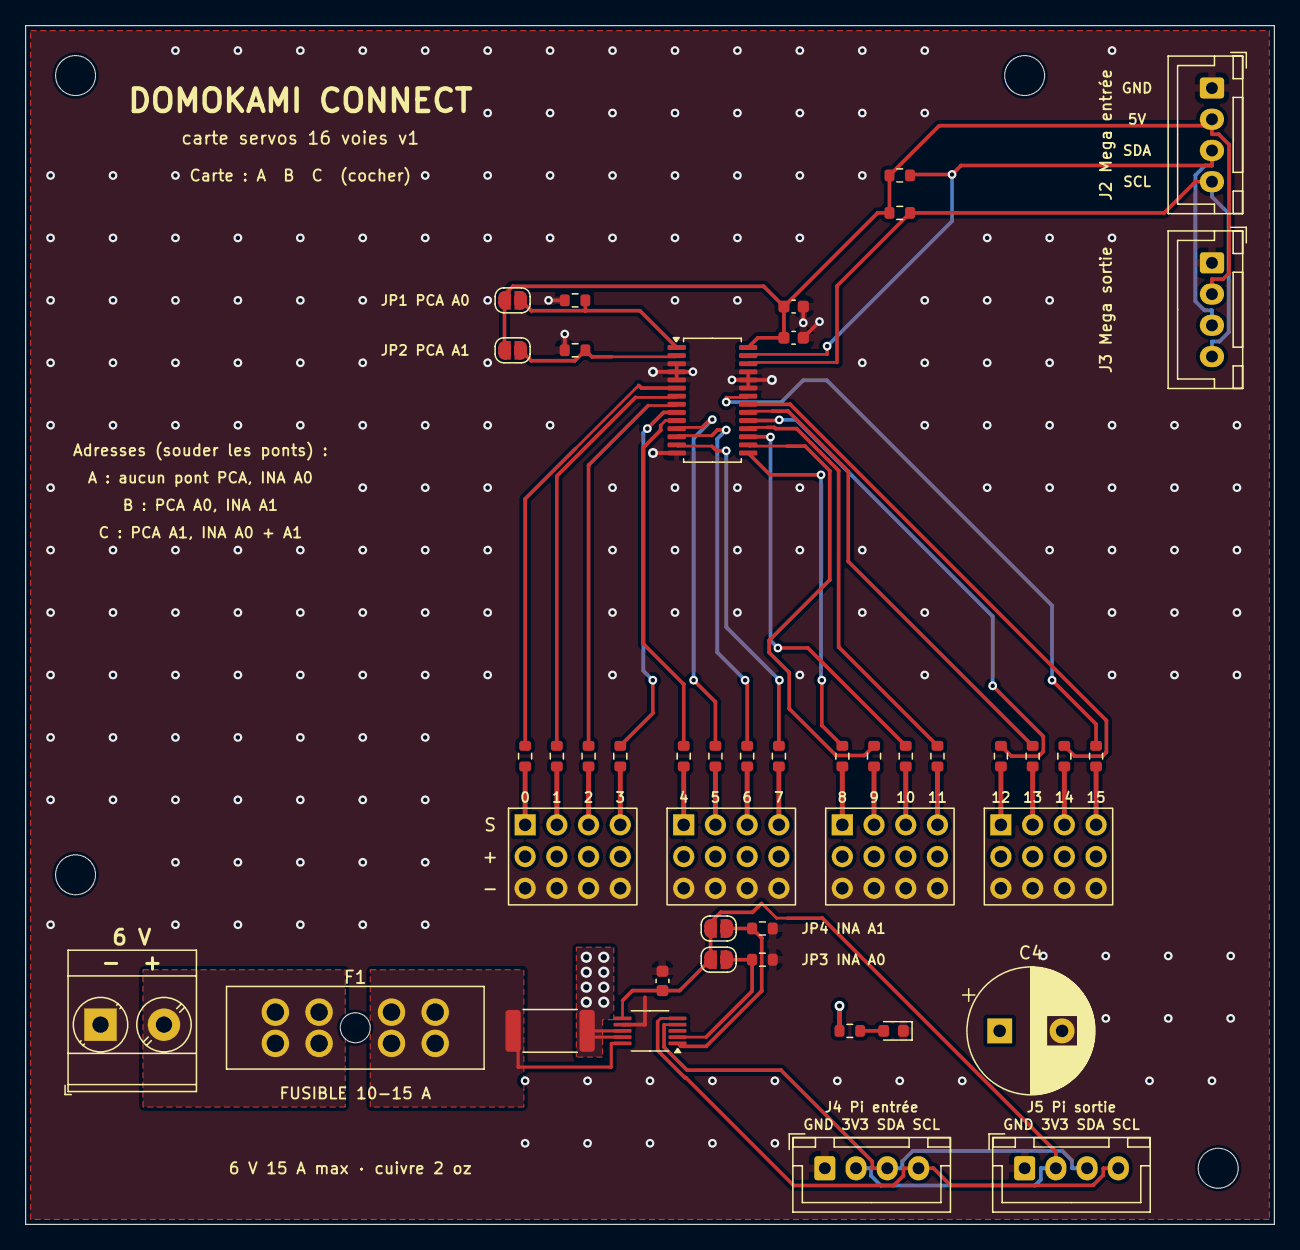
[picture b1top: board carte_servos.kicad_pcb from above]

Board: 2 copper layers, 100.0 x 96.0 mm, 49 parts (0 on the bottom side), 47 nets.

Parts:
C1: 10uF; C_0603_1608Metric
C2, C3: 100nF; C_0603_1608Metric
C4: 1000uF; CP_Radial_D10.0mm_P5.00mm
D1: LED; LED_0603_1608Metric
F1: Fusible ATO; FuseHolder_Blade_ATO_Littelfuse_FLR_178.6165
H1, H2, H3, H4: M3; MountingHole_3.2mm_M3
J1: 6V entrée; TerminalBlock_Phoenix_MKDS-3-2-5.08_1x02_P5.08mm_Horizontal
J2: Mega entrée; JST_XH_B4B-XH-A_1x04_P2.50mm_Vertical
J3: Mega sortie; JST_XH_B4B-XH-A_1x04_P2.50mm_Vertical
J4: Pi entrée; JST_XH_B4B-XH-A_1x04_P2.50mm_Vertical
J5: Pi sortie; JST_XH_B4B-XH-A_1x04_P2.50mm_Vertical
J10: Servos 0-3; Servo_4x3_P2.54mm
J11: Servos 4-7; Servo_4x3_P2.54mm
J12: Servos 8-11; Servo_4x3_P2.54mm
J13: Servos 12-15; Servo_4x3_P2.54mm
JP1: PCA A0; SolderJumper-2_P1.3mm_Open_RoundedPad1.0x1.5mm
JP2: PCA A1; SolderJumper-2_P1.3mm_Open_RoundedPad1.0x1.5mm
JP3: INA A0; SolderJumper-2_P1.3mm_Open_RoundedPad1.0x1.5mm
JP4: INA A1; SolderJumper-2_P1.3mm_Open_RoundedPad1.0x1.5mm
R1, R2, R3, R4, R5, R6, R7, R8, R9, R10, R11, R12, R13, R14, R15, R16: 220; R_0603_1608Metric
R17, R18, R19, R20, R21, R22: 10k; R_0603_1608Metric
R25: 1k; R_0603_1608Metric
RS1: 2mR; R_2512_6332Metric
U1: PCA9685; TSSOP-28_4.4x9.7mm_P0.65mm
U2: INA226; VSSOP-10_3x3mm_P0.5mm

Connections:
+3V3_PI: C3.1, J4.2, J5.2, JP3.1, JP4.1, U2.6
+5V_M: C1.1, C2.1, J2.2, J3.2, JP1.1, JP2.1, R19.1, R20.1, U1.28
+6V: C4.1, J10.2, J10.5, J10.8, J10.11, J11.2, J11.5, J11.8, J11.11, J12.2, J12.5, J12.8, J12.11, J13.2, J13.5, J13.8, J13.11, R25.1, RS1.2, U2.8, U2.9
+6V_F: F1.2, RS1.1, U2.10
+6V_IN: F1.1, J1.2
GND: C1.2, C2.2, C3.2, C4.2, D1.1, J1.1, J2.1, J3.1, J4.1, J5.1, J10.3, J10.6, J10.9, J10.12, J11.3, J11.6, J11.9, J11.12, J12.3, J12.6, J12.9, J12.12, J13.3, J13.6, J13.9, J13.12, R17.1, R18.1, R21.2, R22.2, U1.3, U1.4, U1.5, U1.14, U1.23, U1.24, U1.25, U2.7
INA_A0: JP3.2, R21.1, U2.2
INA_A1: JP4.2, R22.1, U2.1
LED0: R1.2, U1.6
LED1: R2.2, U1.7
LED2: R3.2, U1.8
LED3: R4.2, U1.9
LED4: R5.2, U1.10
LED5: R6.2, U1.11
LED6: R7.2, U1.12
LED7: R8.2, U1.13
LED8: R9.2, U1.15
LED9: R10.2, U1.16
LED10: R11.2, U1.17
LED11: R12.2, U1.18
LED12: R13.2, U1.19
LED13: R14.2, U1.20
LED14: R15.2, U1.21
LED15: R16.2, U1.22
LED_A: D1.2, R25.2
PCA_A0: JP1.2, R17.2, U1.1
PCA_A1: JP2.2, R18.2, U1.2
S0: J10.1, R1.1
S1: J10.4, R2.1
S2: J10.7, R3.1
S3: J10.10, R4.1
S4: J11.1, R5.1
S5: J11.4, R6.1
S6: J11.7, R7.1
S7: J11.10, R8.1
S8: J12.1, R9.1
S9: J12.4, R10.1
S10: J12.7, R11.1
S11: J12.10, R12.1
S12: J13.1, R13.1
S13: J13.4, R14.1
S14: J13.7, R15.1
S15: J13.10, R16.1
SCL_M: J2.4, J3.4, R20.2, U1.26
SCL_P: J4.4, J5.4, U2.5
SDA_M: J2.3, J3.3, R19.2, U1.27
SDA_P: J4.3, J5.3, U2.4

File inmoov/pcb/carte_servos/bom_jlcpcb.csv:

Comment,Designator,Footprint,LCSC Part #
100nF,"C3,C2",C_0603_1608Metric,C14663
10k,"R21,R22,R17,R18,R19,R20",R_0603_1608Metric,C25804
10uF,C1,C_0603_1608Metric,C19702
1k,R25,R_0603_1608Metric,C21190
220,"R1,R2,R3,R4,R5,R6,R7,R8,R9,R10,R11,R12,R13,R14,R15,R16",R_0603_1608Metric,C22962
2mR,RS1,R_2512_6332Metric,C2904228
INA226,U2,VSSOP-10_3x3mm_P0.5mm,C49851
LED,D1,LED_0603_1608Metric,C12624
PCA9685,U1,TSSOP-28_4.4x9.7mm_P0.65mm,C2678753

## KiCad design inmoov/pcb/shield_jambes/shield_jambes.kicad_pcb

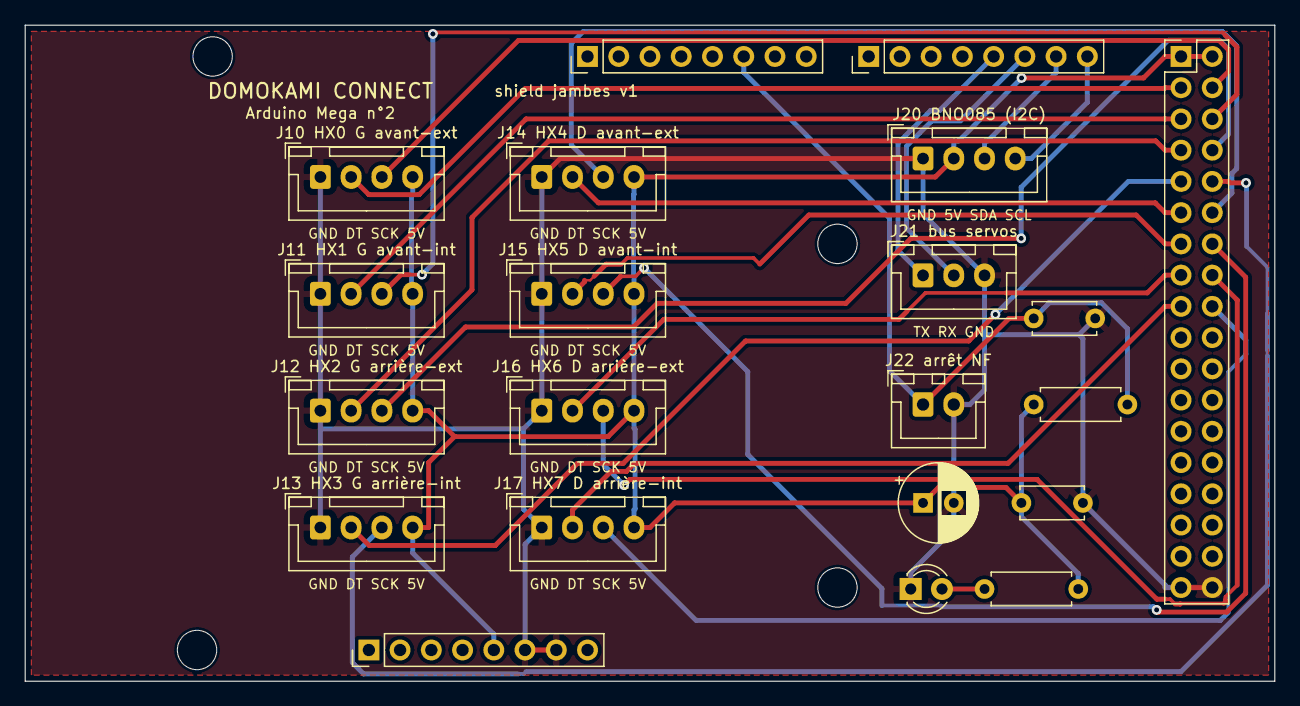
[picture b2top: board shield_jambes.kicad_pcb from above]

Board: 2 copper layers, 101.6 x 53.3 mm, 25 parts (0 on the bottom side), 24 nets.

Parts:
C1, C3: 100nF; C_Disc_D5.0mm_W2.5mm_P5.00mm
C2: 100uF; CP_Radial_D6.3mm_P2.50mm
D1: LED; LED_D3.0mm
H1, H2, H3, H4: M3; MountingHole_3.2mm_M3
J1, J2, J3: Barrette Mega; PinHeader_1x08_P2.54mm_Vertical
J4: Barrette Mega; PinHeader_2x18_P2.54mm_Vertical
J10: HX711 n°0; JST_XH_B4B-XH-A_1x04_P2.50mm_Vertical
J11: HX711 n°1; JST_XH_B4B-XH-A_1x04_P2.50mm_Vertical
J12: HX711 n°2; JST_XH_B4B-XH-A_1x04_P2.50mm_Vertical
J13: HX711 n°3; JST_XH_B4B-XH-A_1x04_P2.50mm_Vertical
J14: HX711 n°4; JST_XH_B4B-XH-A_1x04_P2.50mm_Vertical
J15: HX711 n°5; JST_XH_B4B-XH-A_1x04_P2.50mm_Vertical
J16: HX711 n°6; JST_XH_B4B-XH-A_1x04_P2.50mm_Vertical
J17: HX711 n°7; JST_XH_B4B-XH-A_1x04_P2.50mm_Vertical
J20: BNO085; JST_XH_B4B-XH-A_1x04_P2.50mm_Vertical
J21: Bus servos; JST_XH_B3B-XH-A_1x03_P2.50mm_Vertical
J22: Arret urgence; JST_XH_B2B-XH-A_1x02_P2.50mm_Vertical
R1: 4,7k; R_Axial_DIN0207_L6.3mm_D2.5mm_P7.62mm_Horizontal
R2: 1k; R_Axial_DIN0207_L6.3mm_D2.5mm_P7.62mm_Horizontal

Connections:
+5V: C2.1, C3.1, J1.5, J4.1, J4.2, J10.4, J11.4, J12.4, J13.4, J14.4, J15.4, J16.4, J17.4, J20.2, R1.1, R2.2
ARRET: C1.1, J2.6, J22.1, R1.2
GND: C1.2, C2.2, C3.2, D1.1, J1.6, J1.7, J4.35, J4.36, J10.1, J11.1, J12.1, J13.1, J14.1, J15.1, J16.1, J17.1, J20.1, J21.3, J22.2
HX0_DT: J4.3, J10.2
HX0_SCK: J4.4, J10.3
HX1_DT: J4.5, J11.2
HX1_SCK: J4.6, J11.3
HX2_DT: J4.7, J12.2
HX2_SCK: J4.8, J12.3
HX3_DT: J4.9, J13.2
HX3_SCK: J4.10, J13.3
HX4_DT: J4.11, J14.2
HX4_SCK: J4.12, J14.3
HX5_DT: J4.13, J15.2
HX5_SCK: J4.14, J15.3
HX6_DT: J4.15, J16.2
HX6_SCK: J4.16, J16.3
HX7_DT: J4.17, J17.2
HX7_SCK: J4.18, J17.3
LED_A: D1.2, R2.1
RX1: J3.6, J21.2
SCL: J3.8, J20.4
SDA: J3.7, J20.3
TX1: J3.5, J21.1

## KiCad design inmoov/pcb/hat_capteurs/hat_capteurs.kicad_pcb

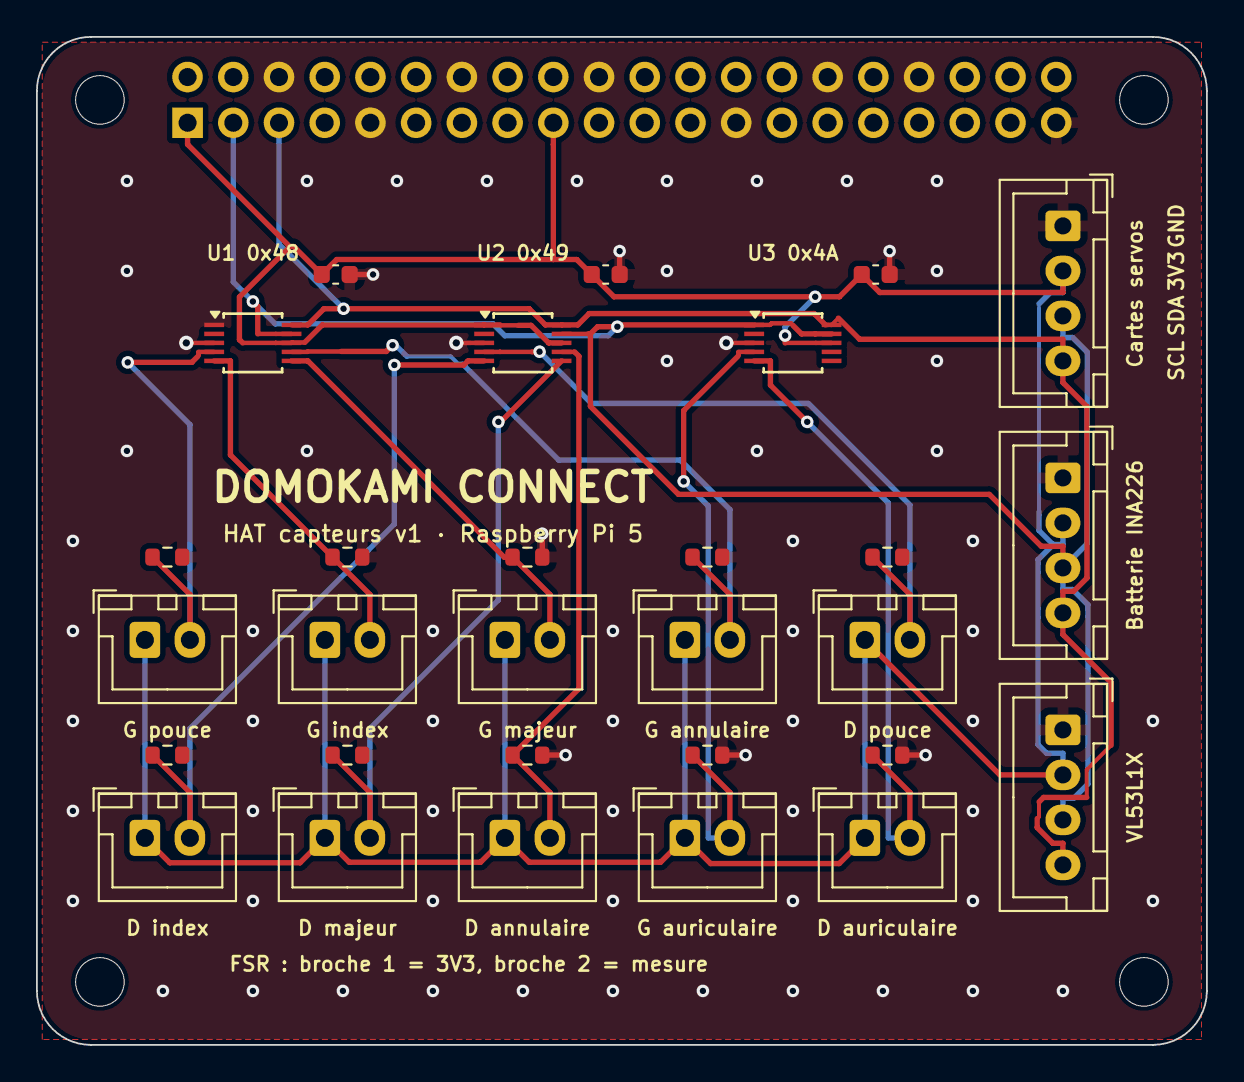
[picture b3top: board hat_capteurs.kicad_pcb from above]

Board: 2 copper layers, 65.0 x 56.0 mm, 34 parts (1 on the bottom side), 14 nets.

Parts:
C1, C2, C3: 100nF; C_0603_1608Metric
H1, H2, H3, H4: M2.5; MountingHole_2.7mm_M2.5
J1: Raspberry Pi; PinSocket_2x20_P2.54mm_Vertical
J2: Cartes servos; JST_XH_B4B-XH-A_1x04_P2.50mm_Vertical
J3: Batterie INA226; JST_XH_B4B-XH-A_1x04_P2.50mm_Vertical
J4: VL53L1X; JST_XH_B4B-XH-A_1x04_P2.50mm_Vertical
J10: G pouce; JST_XH_B2B-XH-A_1x02_P2.50mm_Vertical
J11: G index; JST_XH_B2B-XH-A_1x02_P2.50mm_Vertical
J12: G majeur; JST_XH_B2B-XH-A_1x02_P2.50mm_Vertical
J13: G annulaire; JST_XH_B2B-XH-A_1x02_P2.50mm_Vertical
J14: D pouce; JST_XH_B2B-XH-A_1x02_P2.50mm_Vertical
J15: D index; JST_XH_B2B-XH-A_1x02_P2.50mm_Vertical
J16: D majeur; JST_XH_B2B-XH-A_1x02_P2.50mm_Vertical
J17: D annulaire; JST_XH_B2B-XH-A_1x02_P2.50mm_Vertical
J18: G auriculaire; JST_XH_B2B-XH-A_1x02_P2.50mm_Vertical
J19: D auriculaire; JST_XH_B2B-XH-A_1x02_P2.50mm_Vertical
R1, R2, R3, R4, R5, R6, R7, R8, R9, R10: 10k; R_0603_1608Metric
U1, U2, U3: ADS1115; TSSOP-10_3x3mm_P0.5mm

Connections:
+3V3: C1.1, C2.1, C3.1, J1.1, J1.17, J2.2, J3.2, J4.2, J10.1, J11.1, J12.1, J13.1, J14.1, J15.1, J16.1, J17.1, J18.1, J19.1, U1.8, U2.1, U2.8, U3.8
GND: C1.2, C2.2, C3.2, J1.6, J1.9, J1.14, J1.20, J1.25, J1.30, J1.34, J1.39, J2.1, J3.1, J4.1, R1.2, R2.2, R3.2, R4.2, R5.2, R6.2, R7.2, R8.2, R9.2, R10.2, U1.1, U1.3, U2.3, U3.3
SCL: J1.5, J2.4, J3.4, J4.4, U1.10, U2.10, U3.10
SDA: J1.3, J2.3, J3.3, J4.3, U1.9, U2.9, U3.1, U3.9
U1_A0: J10.2, R1.1, U1.4
U1_A1: J11.2, R2.1, U1.5
U1_A2: J12.2, R3.1, U1.6
U1_A3: J13.2, R4.1, U1.7
U2_A0: J14.2, R5.1, U2.4
U2_A1: J15.2, R6.1, U2.5
U2_A2: J16.2, R7.1, U2.6
U2_A3: J17.2, R8.1, U2.7
U3_A0: J18.2, R9.1, U3.4
U3_A1: J19.2, R10.1, U3.5

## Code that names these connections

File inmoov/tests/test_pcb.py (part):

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
    def test_bus_imu_and_estop(self):
        self.assertIn("ESTOP_PIN         = 2", self.fw)
        self.assertEqual(self.nets["J2"]["6"], "ARRET")            # J2 : D7..D0, pastille 6 = D2
        j3 = self.nets["J3"]                                       # J3 : D14..D21
        self.assertEqual((j3["5"], j3["6"], j3["7"], j3["8"]), ("TX1", "RX1", "SDA", "SCL"))
        self.assertEqual(self.nets["J21"], {"1": "TX1", "2": "RX1", "3": "GND"})
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    def test_servo_outputs(self):
        u1 = self.nets["U1"]
        for i in range(16):
            led_pin = 6 + i if i < 8 else 7 + i            # LED0-7 = 6-13, LED8-15 = 15-22
            self.assertEqual(u1[str(led_pin)], "LED%d" % i)
            self.assertEqual(self.nets["R%d" % (i + 1)], {"1": "S%d" % i, "2": "LED%d" % i})
            block = self.nets["J%d" % (10 + i // 4)]
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
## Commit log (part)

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2026-05-27 feat: VCore 3.1 / RatOS v2.1 configurator with probe & bed mesh
    Complete Klipper configuration tool for VCore 3.1 CoreXY printer:
    - Printer settings: size (300/400/500mm), board, extruder, hotend
    - Probe configurator: Beacon, Cartographer, Klicky, Euclid, BL-Touch, CR-Touch
    with visual offset diagram and per-probe defaults
    - Bed mesh map: zone config, grid resolution (3–11 pts), algorithm (bicubic/lagrange),
    fade settings, simulated heatmap with heat coloring and stats
